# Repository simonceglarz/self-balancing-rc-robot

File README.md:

# ESP32 Self-Balancing Robot

A two-wheeled self-balancing robot built around an ESP32, an IMU, and a cascaded PID control loop — with a live WiFi tuning interface and a dedicated wireless joystick controller.

   [Full-length demo (27s, MP4)](media/balance_full.mp4)
## Overview

This robot balances on two wheels using a complementary filter for orientation estimation and a two-loop (cascaded) PID controller: an inner loop holds the body upright, and an outer loop corrects for long-term drift by tracking wheel velocity from quadrature encoders. It can be driven and steered two ways — a phone/browser joystick served directly from the robot's own WiFi access point, or a dedicated physical ESP32 + analog-joystick controller communicating over ESP-NOW.

## Features

- **Cascaded PID control** — inner loop (angle) + outer loop (velocity/drift), tuned live rather than by reflashing
- **WiFi live-tuning webpage** — the ESP32 hosts its own access point and a WebSocket-driven page with sliders for every gain, calibration constant, and per-motor floor, plus a draggable on-screen joystick for driving
- **Physical joystick controller** — a second ESP32 reading an analog joystick, sending continuous steering data over ESP-NOW (no phone required, lower latency than WiFi)
- **Per-motor stiction compensation** — independently tunable output floors and a proportional rescale, since the two motors' real-world behavior isn't identical
- **Hysteresis-based deadband** — a Schmitt-trigger style engage/disengage threshold to suppress motor chatter at equilibrium without losing responsiveness to small corrections
- **Smoothly ramped inputs** — commanded lean/steer values slew toward their target instead of stepping instantly, avoiding derivative-kick spikes
- **OLED live telemetry** — angle, motor output, encoder-derived velocity, battery voltage, and a small tilt-indicator graphic

## Hardware

| Component | Notes |
|---|---|
| ESP32 dev board (x2) | one for the robot, one for the joystick controller |
| Adafruit LSM6DSOX | 6-axis IMU (accelerometer + gyro) |
| SSD1306 OLED (128x64, I2C) | onboard telemetry display |
| 2x DC motor + quadrature encoders | drive + odometry |
| Motor driver (dual H-bridge) | AIN1/AIN2, BIN1/BIN2 control |
| 2-axis analog joystick module | physical controller input |
| LiPo battery + voltage divider | robot power + monitoring via `analogReadMilliVolts()` |
| Buck regulator (Adafruit MPM3610, 5V) | steps the 7.4V 2S LiPo down to 5V for the ESP32 |
| Reverse-polarity protection (1N5822 Schottky) | sits ahead of the buck input, ~0.35V drop |

## Build

| | |
|---|---|
|  |  |
| Assembled 3-layer 3D-printed chassis — top plate carries the LiPo battery and OLED, middle plate holds the ESP32, IMU, and perfboard wiring, bottom plate mounts the motor driver. Brass standoffs separate the layers. | Rear view showing inter-layer wiring and one of the two drive wheels. |

## Architecture

```
IMU (accel + gyro) ──► complementary filter ──► angle estimate
                                                     │
                          ┌──────────────────────────┘
                          ▼
              inner loop: PID(Kp, Ki, Kd) on angle error
                          │
              outer loop: velocity/drift correction
              (encoder-derived velocity → Kp_vel/Ki_vel → shifts
               the angle setpoint to correct long-term drift)
                          │
                          ▼
        per-motor floor rescale + hysteresis deadband
                          │
                          ▼
                   motorA() / motorB() (PWM)
```

Input arrives from either the WebSocket ('J:x:y' from the webpage joystick, or discrete gain/calibration updates from the tuning sliders) or ESP-NOW (the physical joystick controller) — both write into the same `targetAngleTrim`/`steerBias` variables, so the control loop doesn't care which source is driving it.

## Power Architecture
2S LiPo (7.4V nominal, 8.4V full)
             │
             ▼
1N5822 Schottky diode (reverse-polarity protection, ~0.35V drop)
      │ 
      ▼
power node ──┬── DRV8833 VM (motors run off the unregulated battery rail)
             ├── 2× 1000µF bulk caps + 100nF ceramic → GND
             └── MPM3610 buck regulator (Vin)
                    │
                    ▼
               5V out → ESP32 5V pin
             │
             ▼
ESP32 internal LDO → 3.3V rail
	    │
┌───────────┼───────────┐
▼           ▼           ▼
IMU + OLED Encoder VCC DRV8833 SLP
   (I2C)     (must be held high or driver sleeps)

Motors draw directly off the unregulated battery rail (through the protection diode) since they don't need clean power; logic and sensors run off the regulated 5V → 3.3V chain, which does.

**Bench-verified (multimeter):**

| Measurement point | Reading |
|---|---|
| Diode cathode (post-protection) | 8.05 V |
| MPM3610 output | 5.00 V |
| ESP32 3.3V pin | 3.32 V |
| Battery rail under full motor load | 7.77 V (no sag — bulk caps holding) |

## Custom PCB (rev 1)

The perfboard is being replaced by a 2-layer KiCad PCB (120 \C3\97 70 mm) that carries the ESP32, motor driver and buck converter on sockets.

- Separate I2C bus for the IMU, so OLED refreshes (~23 ms) can't delay the 100 Hz control loop
- 8 GPIOs remapped so motor and encoder traces route without crossings; selected in firmware with `#define PCB_REV1`
- Trace widths sized by current (1.5 mm battery, 1.0 mm motor, 0.5 mm 5 V)
- 20-pin expansion header for v2 add-ons: servos, I2S speaker, UART and extra I2C sensors
- Debug headers for motor PWM and encoder signals that sit under the modules

**Status:** ordered from JLCPCB, bring-up in progress. Full write-up, pinouts and design notes: [`pcb/README.md`](pcb/README.md)

## Setup

Each firmware is its own PlatformIO project.

**Robot** (`robot/`):
1. `pio run --target upload` from within `robot/`
2. Power on, open the serial monitor (115200 baud) — it prints the WiFi AP IP and its ESP-NOW MAC address
3. Connect a phone/laptop to the `BalanceBot` AP and open `http://<AP IP>/` for the tuning page

**Controller** (`controller/`):
1. Wire the joystick module: VRx→GPIO34, VRy→GPIO35, SW→GPIO32, VCC→3.3V, GND→GND
2. Set `robotMac[]` in `controller/src/main.cpp` to the robot's printed AP MAC address
3. Confirm `WIFI_CHANNEL` matches between both projects
4. `pio run --target upload` from within `controller/`

Both projects are pinned to the same platform version (see each `platformio.ini`) — this matters, since ESP-NOW callback signatures changed between core versions and mismatched cores between the two boards can cause hard-to-diagnose link failures.

## Debugging notes / what I actually learned building this

- **Output floor destroyed proportionality.** A flat "snap any nonzero output up to the motor's stiction floor" made the controller bang-bang, not proportional, for the entire range under a few degrees of error — the majority of actual operating time. Fixed by rescaling the output range onto `[MIN_OUTPUT, MAX_OUTPUT]` per motor instead of snapping.
- **Encoder velocity math is a real kinematics problem, not an arbitrary sign choice.** Diagnosing whether `avgVelocity` should combine the two encoders by addition or subtraction meant understanding what each raw sign actually meant physically (translation vs. yaw), not just trying both and picking whichever "looked less bad." Verified empirically with a manual push test (motors disabled, print raw deltas) rather than guessing.
- **A control loop can have the wrong sign of an otherwise-correct formula.** Reversing the encoder combination made the outer loop feed real motion back into itself as *positive* feedback instead of negative — the difference between correcting drift and amplifying it into a runaway, from one flipped sign.
- **Deadbands need hysteresis, not a single threshold.** A flat deadband still has exactly one crossing point, and standing-still equilibrium sits right on top of it — sensor noise flickering across that single threshold was the actual jitter, not "too much" or "too little" deadband. A two-threshold (engage/disengage) hysteresis fixed it structurally instead of by tuning a magic number.
- **A hard on/off switch in a control loop creates a real discontinuity.** Suppressing the outer loop during a turn (to stop it reacting to a turn-induced phantom velocity reading) fixed the turn-tipping, but re-enabling it instantly the moment steering stopped caused a visible jerk — full-strength correction plus whatever stale value existed applied in a single tick. Replaced with a ramped suppression factor.

## Known limitations / open items

- `ANGLE_TRIM_DEG` (the sensor-to-mechanical zero offset) drifts somewhat run-to-run; auto-calibration was considered but not implemented.
- Turning still relies on suppressing the outer loop rather than a from-first-principles kinematic decoupling of translation and rotation.
- No IMU cross-axis leakage compensation (untested whether it's actually present on this build).

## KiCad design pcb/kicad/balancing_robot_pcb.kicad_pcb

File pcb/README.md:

# Custom PCB: Rev 1

A 2-layer KiCad PCB that replaces the robot's hand-wired perfboard. It carries the ESP32 DevKit, the DRV8833 motor driver and the 5 V buck on sockets, and adds a dedicated motor-control and sensor layout plus an expansion header for v2 features.

**Status (Oct 2026):** layout complete, DRC clean, ordered from JLCPCB. Bring-up and testing on the robot are next. This page will be updated with measurements.

| Front | Back |
|---|---|
|  |  |

---

## Board summary

| Item | Value |
|---|---|
| Size | 120 × 70 mm, rounded corners, 4 × M3 mounting holes |
| Stack-up | 2 layers, 1.6 mm FR4, 1 oz copper |
| Assembly | All through-hole, hand-soldered |
| Modules (socketed) | ESP32-WROOM DevKit (38-pin), Adafruit DRV8833, Adafruit MPM3610 5 V buck |
| Power input | 2S LiPo (7.4 V) via XT60 → toggle switch → 1N5822 Schottky (reverse polarity) → 2 × 1000 µF + 100 nF |
| Connectors | JST-XH for motors and encoders; 0.1" headers for IMU, OLED and two I2C ports; 2 × 10 expansion socket |
| Ground | Poured on both layers, stitched with vias |
| DRC | 0 errors, 0 unconnected items |
| Tools | KiCad 9, JLCPCB |

---

## Design decisions

### 1. Modules on sockets instead of bare chips
The ESP32, motor driver and buck all plug in as breakout boards. A bare ESP32 module would have needed USB, auto-reset and boot circuitry, and the DRV8833 IC comes in an HTSSOP package with a thermal pad that isn't practical to hand-solder. Socketing also means a damaged module can be swapped without desoldering, which matters on a robot that falls over during tuning.

### 2. Traces sized by current
Trace widths come from net classes, sized with IPC-2221 for 1 oz outer copper and a ~10 °C rise:

| Net class | Nets | Width | Expected current |
|---|---|---|---|
| Battery | Battery input, switch, diode, VBAT rail | 1.5 mm | ~2–3 A continuous (both motors + logic, headroom for servos) |
| Motor | DRV8833 outputs | 1.0 mm | up to ~1.2 A continuous / 2 A peak per channel |
| 5V | Buck output | 0.5 mm | up to 1.2 A (MPM3610 limit) |
| Default | Signals, 3.3 V | 0.25 mm | well under 0.5 A |

### 3. Two I2C buses
On the perfboard the IMU and OLED shared one bus. A full SSD1306 refresh is ~1 KB, roughly 23 ms at 400 kHz, which is longer than two 10 ms control-loop periods. The PCB gives the IMU its own bus (GPIO 19/18) and moves the OLED and all future I2C devices to a second bus (GPIO 21/22), so a display update can never delay an IMU read.

### 4. GPIO remapping for clean routing
The perfboard pin assignments forced the motor-control and encoder traces to cross the board. Because the ESP32's PWM and input pins are interchangeable for these signals, I reassigned 8 GPIOs so each group runs straight from its connector to the ESP32 with no crossings:

| Signal | Perfboard GPIO | PCB GPIO |
|---|---|---|
| Motor A IN1 / IN2 | 26 / 32 | 32 / 33 |
| Motor B IN1 / IN2 | 25 / 33 | 26 / 25 |
| Encoder A ch. A / B | 27 / 14 | 34 / 35 |
| Encoder B ch. A / B | 34 / 35 | 27 / 14 |
| OLED SDA / SCL | 19 / 18 (shared) | 21 / 22 (own bus) |

The firmware selects the mapping with a single `#define PCB_REV1` switch, so the same code runs on both the perfboard and the PCB.

### 5. Expansion header for v2
A 2 × 10 female socket (J15) exposes everything a future daughterboard needs: battery, 5 V, 3.3 V, the second I2C bus, UART2, I2S (for a speaker amp), two servo PWM pins and one ADC1 input.
- **Safe pins only.** ESP32 strapping pins (GPIO 0, 2, 12) are left off, so a daughterboard can never stop the robot from booting. GPIO 5 and 15 are only used for I2S, where a glitch at boot is harmless.
- **ADC1 only.** The analog input is GPIO39, because ADC2 doesn't work while WiFi is on.
- **Power pins fenced by ground.** A solder bridge between neighbouring pins can't short 8.4 V onto 3.3 V.
- **Female socket**, so battery voltage is never on exposed pins.
- Servos and audio are meant to get their own regulator on the daughterboard, fed from the battery pins, since the MPM3610 is limited to 1.2 A.

### 6. Signal integrity on a 2-layer board
- **Solid bottom ground plane.** Almost all routing is on the top layer; the bottom layer is a ground pour, used only for short perpendicular hops.
- **Top ground pour stitched with vias** around the edges, beside bottom-layer hops, and inside dense trace bundles, so isolated copper islands stay grounded.
- **Ordering in the expansion bus.** The I2S clock (BCLK, ~2.8 MHz) runs in the middle of its own group, UART acts as a buffer between I2S and I2C, and servo lines run next to the 5 V rail. I2C is kept furthest from BCLK because it's open-drain, so a coupled spike on SCL can look like an extra clock edge.
- **Fixing a ground-plane gap.** Three adjacent bottom-layer hops left a ~4 × 2.5 mm hole in the ground pour directly under BCLK's path. Moving the hop to BCLK instead (one via instead of six) closed the gap.
- **Antenna keep-out.** A rule area keeps tracks, vias and copper pours out from under the ESP32's PCB antenna on both layers.
- **High-impedance nodes.** The battery-sense divider node (~32 kΩ) is crossed at right angles only, and filtered with 100 nF (τ ≈ 3.2 ms).

### 7. Debug access
The DevKit and DRV8833 cover their own pins once plugged in, so signals under them get dedicated access:
- **Motor_Debug (J17):** all four motor PWM lines plus ground, in line between the driver and the ESP32.
- **Enc_Debug (J16):** all four filtered encoder channels with ground on both ends.
- **Test points** for VBAT, 5 V, 3.3 V, IMU SDA/SCL and ground.
- **Optional I2C pull-ups** (R8/R9, not fitted by default) for when the connected modules don't provide their own.

---

## Mistakes caught before ordering

| Problem | How it was found | Fix |
|---|---|---|
| DRC reported 499 violations, hitting KiCad's per-type cap and hiding real errors | Every flagged item was silkscreen on the same footprint | An unconditioned custom "physical clearance" rule was checking every footprint's graphics against itself. Deleted it |
| DevKit header rows placed 23.5 mm apart | 23.5 mm isn't a multiple of 0.1"; counted the holes on the perfboard | Caliper error measuring edge-to-edge. Real spacing is 0.9" (22.86 mm) |
| DRV8833 rows placed 13.35 mm apart | Same off-grid check | Took 12.70 mm (0.5") from Adafruit's fabrication drawing |
| XT60 footprint was the same gender as the battery's plug | Pre-order check against the real battery lead | Swapped to the male footprint |
| Power switch had no matching library footprint | Compared the real switch against library parts | Drew a custom footprint to match it |

All module footprints were checked against the real parts before ordering.

---

## Pinouts

**ESP32 DevKit (PCB rev 1)**

| Function | GPIO | Function | GPIO |
|---|---|---|---|
| IMU SDA / SCL (bus A) | 19 / 18 | Motor A IN1 / IN2 | 32 / 33 |
| OLED + ports SDA / SCL (bus B) | 21 / 22 | Motor B IN1 / IN2 | 26 / 25 |
| Encoder A ch. A / B | 34 / 35 | Battery sense (ADC1) | 36 |
| Encoder B ch. A / B | 27 / 14 | Expansion analog in (ADC1) | 39 |

**Expansion header J15** (top row odd, pin 1 = square pad)

| Pin | Net | Pin | Net |
|---|---|---|---|
| 1 | VBAT | 2 | VBAT |
| 3 | GND | 4 | GND |
| 5 | 5V | 6 | GND |
| 7 | GND | 8 | EXP_IN (GPIO39, ADC1, input only) |
| 9 | 3V3 | 10 | UART2 TX (GPIO17) |
| 11 | I2C B SDA (GPIO21) | 12 | UART2 RX (GPIO16) |
| 13 | I2C B SCL (GPIO22) | 14 | I2S LRC (GPIO5) |
| 15 | GND | 16 | I2S BCLK (GPIO23) |
| 17 | Servo 1 (GPIO4) | 18 | I2S DIN (GPIO15) |
| 19 | Servo 2 (GPIO13) | 20 | GND |

**I2C ports J13 / J14:** GND · 3V3 · SDA · SCL (Qwiic pin order on 0.1" headers).

---

## Bring-up plan

1. Visual and DMM check: no shorts from VBAT, 5 V or 3.3 V to ground, and no battery voltage on any module socket pin.
2. Power on with all modules removed and measure every socket pin.
3. Add the buck → check 5 V. Add the DevKit → check 3.3 V. Add the DRV8833 last.
4. Measure the bus B pull-up resistance; fit R8/R9 only if it's open or very high.
5. Run the motor/encoder test with `PCB_REV1 1` to confirm each motor and its encoder.
6. Scope captures: motor PWM, raw vs filtered encoder edges, I2C traffic, and rail dips during motor steps.

---

## Files

| Path | Contents |
|---|---|
| `kicad/` | KiCad 9 project: schematic, layout, custom footprints |
| `gerbers/` | Fabrication files sent to JLCPCB |
| `docs/schematic.pdf` | Schematic export |

---

## Next

- Bring-up results and measurements (rail ripple, encoder edges, motor current).
- Compare WiFi range against the perfboard build, since the board now sits under the antenna.
- Measure motor stall current to confirm whether the DRV8833 (1.2 A per channel) has enough headroom for self-righting, or whether rev 2 needs a stronger driver.
- A possible rev 2 replacing the modules with a bare ESP32 module, the DRV8833 IC and an SMD buck, assembled by the fab.

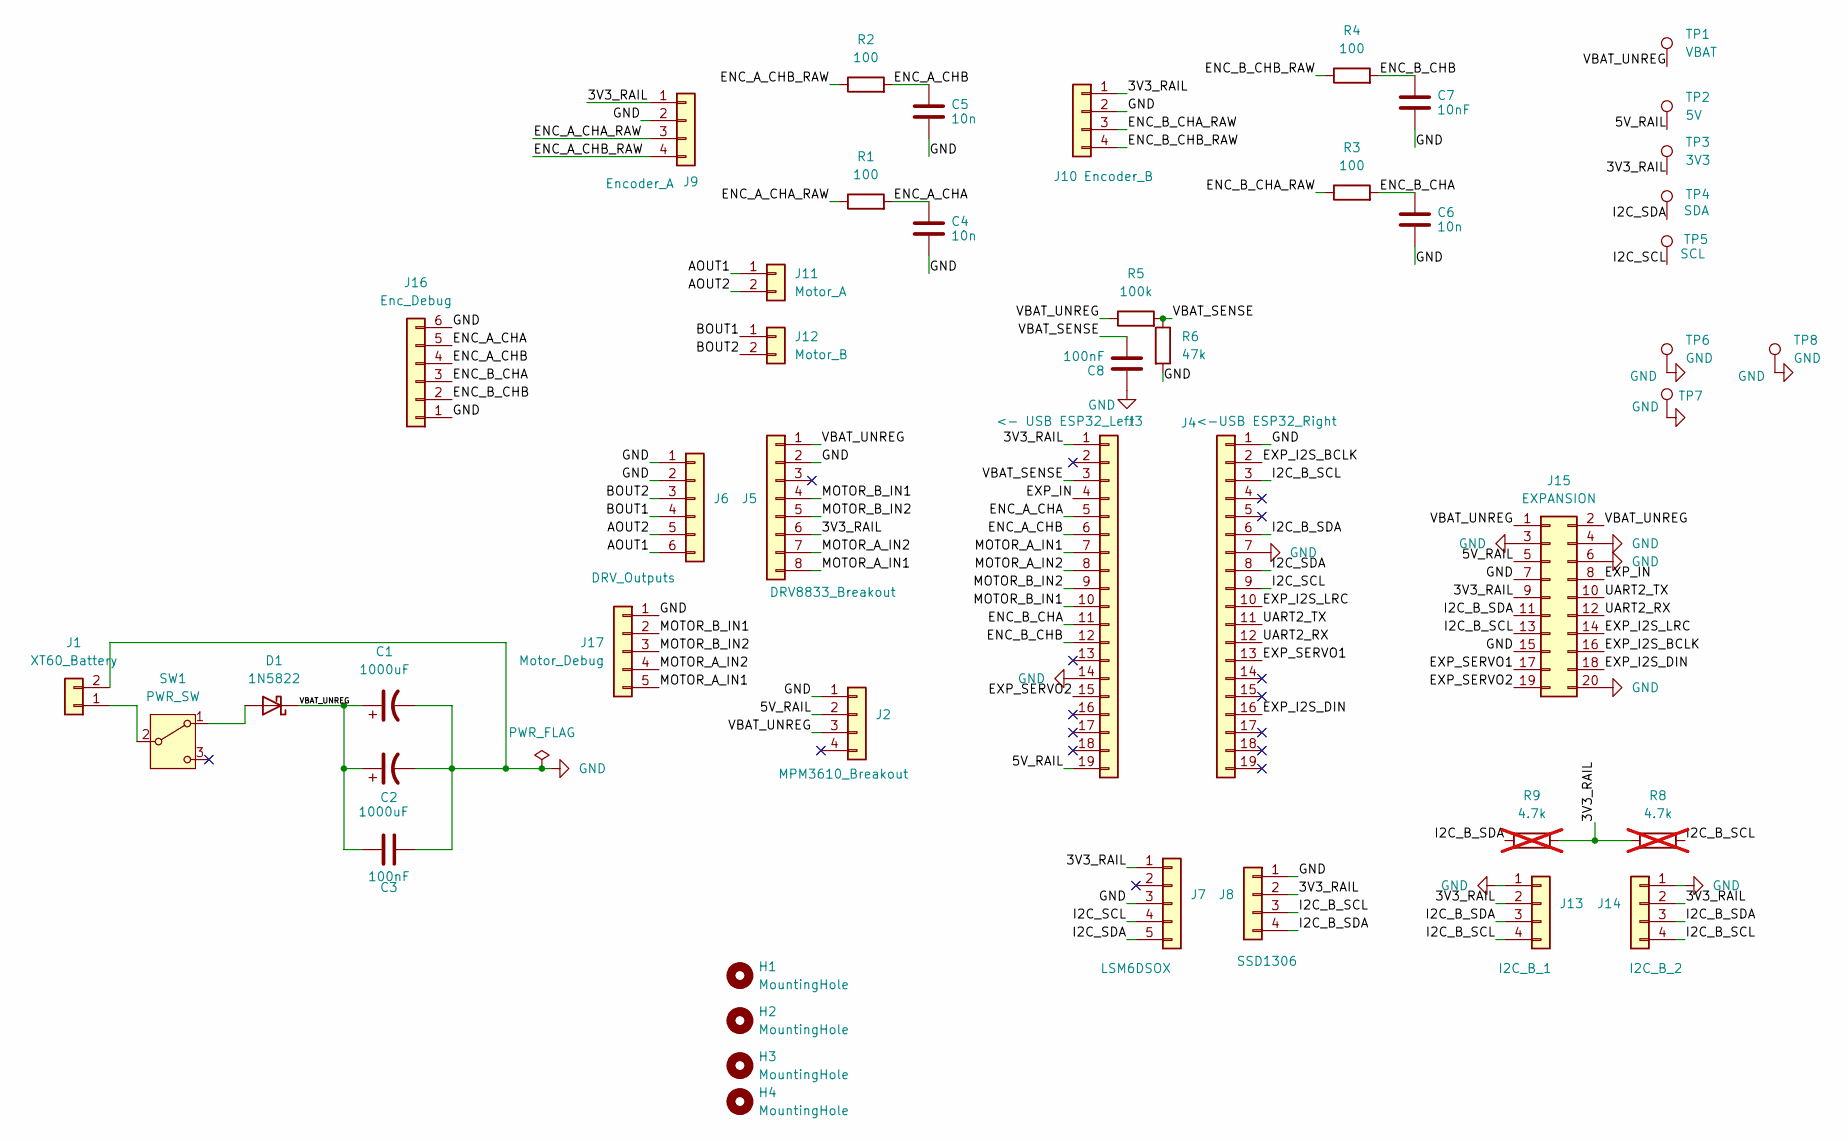
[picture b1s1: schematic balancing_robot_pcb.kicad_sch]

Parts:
C1, C2: 1000uF; CP_Radial_D10.0mm_P5.00mm
C3, C8: 100nF; C_Disc_D3.0mm_W2.0mm_P2.50mm
C4, C5, C6: 10n; C_Disc_D3.0mm_W2.0mm_P2.50mm
C7: 10nF; C_Disc_D3.0mm_W2.0mm_P2.50mm
D1: 1N5822; D_DO-201AD_P15.24mm_Horizontal
H1, H2, H3, H4: MountingHole; MountingHole_3.2mm_M3
J1: XT60_Battery; AMASS_XT60-F_1x02_P7.20mm_Vertical
J2: MPM3610_Breakout; PinSocket_1x04_P2.54mm_Vertical
J3: <- USB ESP32_Left; PinSocket_1x19_P2.54mm_Vertical
J4: <-USB ESP32_Right; PinSocket_1x19_P2.54mm_Vertical
J5: DRV8833_Breakout; PinSocket_1x08_P2.54mm_Vertical
J6: DRV_Outputs; PinSocket_1x06_P2.54mm_Vertical
J7: LSM6DSOX; PinSocket_1x05_P2.54mm_Vertical
J8: SSD1306; PinSocket_1x04_P2.54mm_Vertical
J9: Encoder_A; JST_XH_B4B-XH-A_1x04_P2.50mm_Vertical
J10: Encoder_B; JST_XH_B4B-XH-A_1x04_P2.50mm_Vertical
J11: Motor_A; JST_XH_B2B-XH-A_1x02_P2.50mm_Vertical
J12: Motor_B; JST_XH_B2B-XH-A_1x02_P2.50mm_Vertical
J13: I2C_B_1; PinSocket_1x04_P2.54mm_Vertical
J14: I2C_B_2; PinSocket_1x04_P2.54mm_Vertical
J15: EXPANSION; PinSocket_2x10_P2.54mm_Vertical
J16: Enc_Debug; PinSocket_1x06_P2.54mm_Vertical
J17: Motor_Debug; PinSocket_1x05_P2.54mm_Vertical
R1, R2, R3, R4: 100; R_Axial_DIN0207_L6.3mm_D2.5mm_P10.16mm_Horizontal
R5: 100k; R_Axial_DIN0207_L6.3mm_D2.5mm_P10.16mm_Horizontal
R6: 47k; R_Axial_DIN0207_L6.3mm_D2.5mm_P10.16mm_Horizontal
R8, R9: 4.7k; R_Axial_DIN0207_L6.3mm_D2.5mm_P10.16mm_Horizontal; not fitted
SW1: PWR_SW; SW_MTS102_SPDT_3Pin
TP1: VBAT; TestPoint_THTPad_D2.0mm_Drill1.0mm
TP2: 5V; TestPoint_THTPad_D2.0mm_Drill1.0mm
TP3: 3V3; TestPoint_THTPad_D2.0mm_Drill1.0mm
TP4: SDA; TestPoint_THTPad_D2.0mm_Drill1.0mm
TP5: SCL; TestPoint_THTPad_D2.0mm_Drill1.0mm
TP6, TP7, TP8: GND; TestPoint_THTPad_D2.0mm_Drill1.0mm

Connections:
/3V3_RAIL: J3.1, J5.6, J7.1, J8.2, J9.1, J10.1, J13.2, J14.2, J15.9, R8.1, R9.2, TP3.1 (1_1)
/5V_RAIL: J2.2, J3.19, J15.5, TP2.1 (1_1)
/AOUT1: J6.6, J11.1
/AOUT2: J6.5, J11.2
/BOUT1: J6.4, J12.1
/BOUT2: J6.3, J12.2
/ENC_A_CHA: C4.1, J3.5, J16.5, R1.2
/ENC_A_CHA_RAW: J9.3, R1.1
/ENC_A_CHB: C5.1, J3.6, J16.4, R2.2
/ENC_A_CHB_RAW: J9.4, R2.1
/ENC_B_CHA: C6.1, J3.11, J16.3, R3.2
/ENC_B_CHA_RAW: J10.3, R3.1
/ENC_B_CHB: C7.1, J3.12, J16.2, R4.2
/ENC_B_CHB_RAW: J10.4, R4.1
/EXP_I2S_BCLK: J4.2, J15.16
/EXP_I2S_DIN: J4.16, J15.18
/EXP_I2S_LRC: J4.10, J15.14
/EXP_IN: J3.4, J15.8
/EXP_SERVO1: J4.13, J15.17
/EXP_SERVO2: J3.15, J15.19
/I2C_B_SCL: J4.3, J8.3, J13.4, J14.4, J15.13, R8.2
/I2C_B_SDA: J4.6, J8.4, J13.3, J14.3, J15.11, R9.1
/I2C_SCL: J4.9, J7.4, TP5.1 (1_1)
/I2C_SDA: J4.8, J7.5, TP4.1 (1_1)
/MOTOR_A_IN1: J3.7, J5.8, J17.5
/MOTOR_A_IN2: J3.8, J5.7, J17.4
/MOTOR_B_IN1: J3.10, J5.4, J17.2
/MOTOR_B_IN2: J3.9, J5.5, J17.3
/UART2_RX: J4.12, J15.12
/UART2_TX: J4.11, J15.10
/VBAT_SENSE: C8.2, J3.3, R5.2, R6.1
/VBAT_UNREG: C1.1, C2.1, C3.2, D1.1 (K), J2.3, J5.1, J15.1, J15.2, R5.1, TP1.1 (1_1)
GND: C1.2, C2.2, C3.1, C4.2, C5.2, C6.2, C7.2, C8.1, J1.2, J2.1, J3.14, J4.1, J4.7, J5.2, J6.1, J6.2, J7.3, J8.1, J9.2, J10.2, J13.1, J14.1, J15.3, J15.4, J15.6, J15.7, J15.15, J15.20, J16.1, J16.6, J17.1, R6.2, TP6.1 (1_1), TP7.1 (1_1), TP8.1 (1_1)
unnamed: D1.2 (A), SW1.1 (A)
unnamed: J1.1, SW1.2 (B)

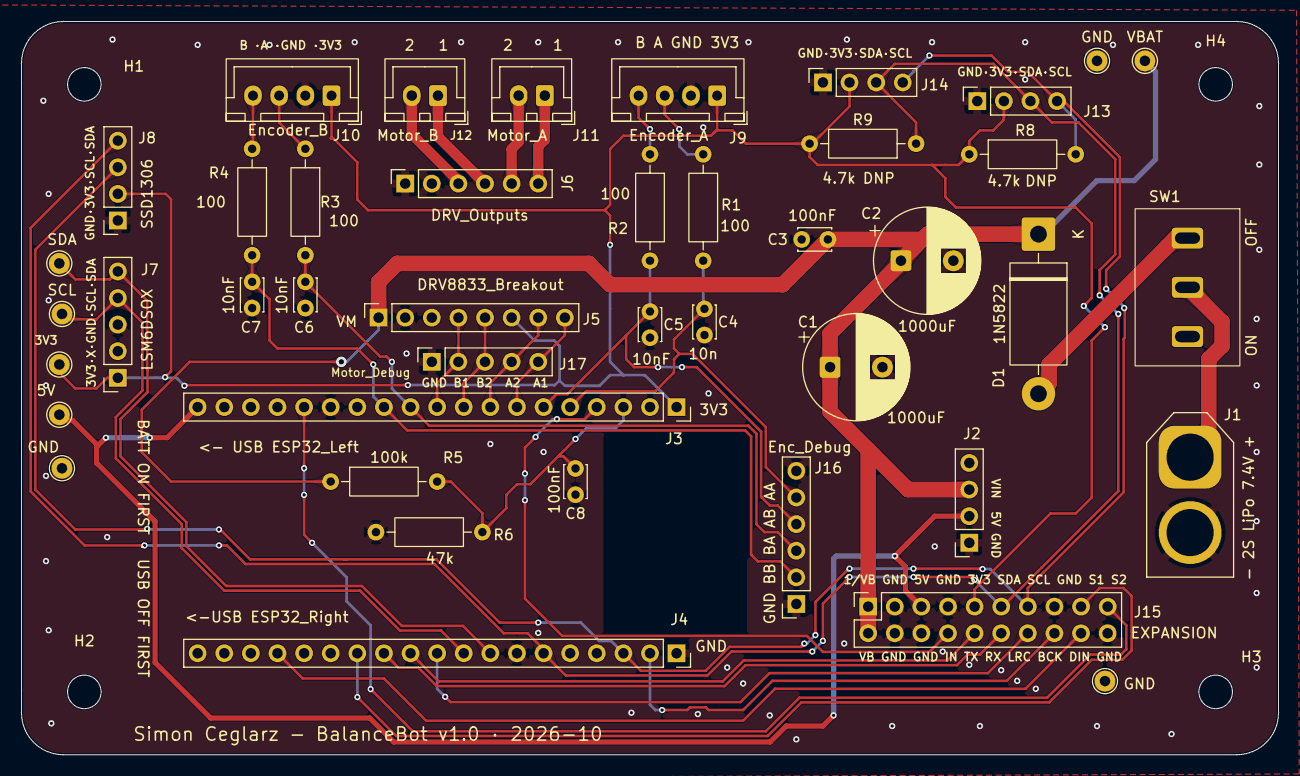
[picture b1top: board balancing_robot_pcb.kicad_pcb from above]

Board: 2 copper layers, 120.0 x 70.0 mm, 48 parts (1 on the bottom side), 35 nets.

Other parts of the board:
LOGO**: QR_LinkedIn_14.8mm
